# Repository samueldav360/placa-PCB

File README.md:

# placa-PCB
hize este proyecto para STASIS hackathon de hackclub

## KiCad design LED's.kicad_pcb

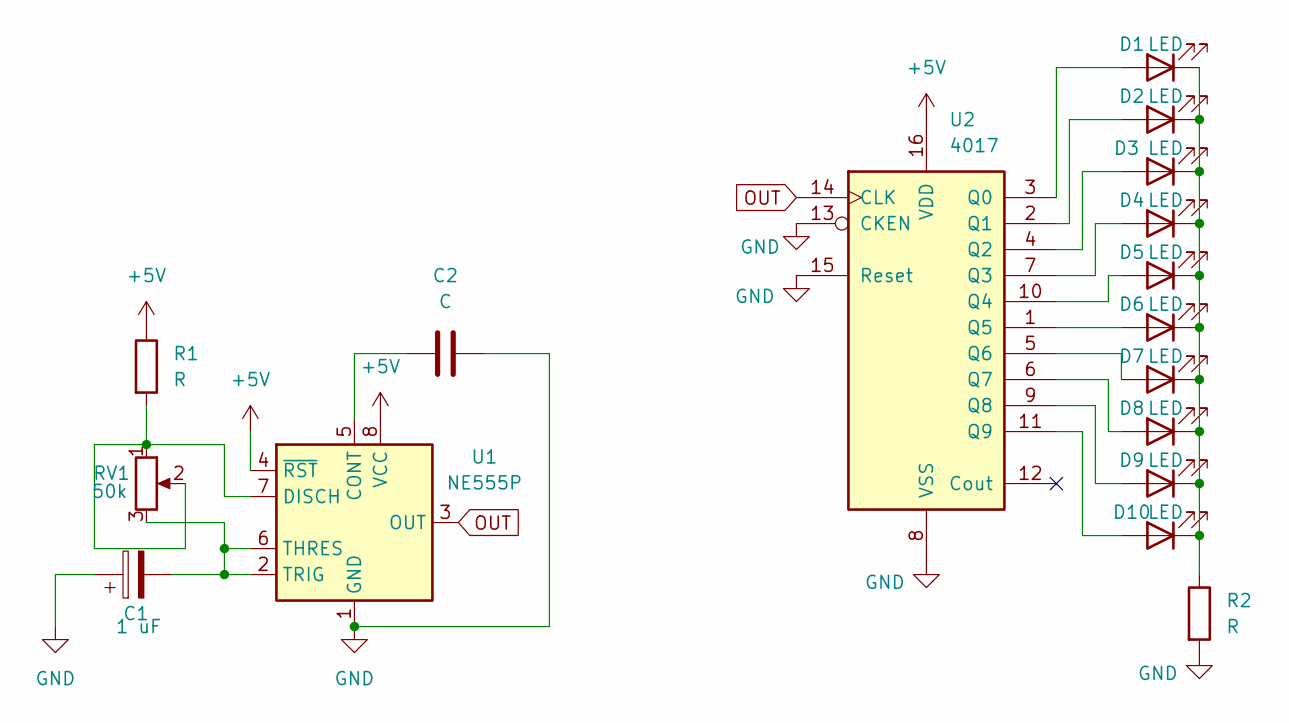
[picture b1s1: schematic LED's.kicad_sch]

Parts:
C1: 1 uF; C_Disc_D3.0mm_W1.6mm_P2.50mm
C2: C; C_Disc_D3.0mm_W1.6mm_P2.50mm
D1, D2, D3, D4, D5, D6, D7, D8, D9, D10: LED; LED_D3.0mm
R1, R2: R; R_Axial_DIN0204_L3.6mm_D1.6mm_P5.08mm_Horizontal
RV1: 50k; Potentiometer_ACP_CA6-VSMD_Vertical
U1: NE555P; DIP-8_W7.62mm
U2: 4017; N16

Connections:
+5V: R1.1, U1.4 (~RST), U1.8 (VCC), U2.16 (VDD)
GND: C1.1, C2.2, R2.2, U1.1 (GND), U2.8 (VSS), U2.13 (CKEN), U2.15 (Reset)
unnamed: D1.2 (A), U2.3 (Q0)
unnamed: D1.1 (K), D2.1 (K), D3.1 (K), D4.1 (K), D5.1 (K), D6.1 (K), D7.1 (K), D8.1 (K), D9.1 (K), D10.1 (K), R2.1
unnamed: D2.2 (A), U2.2 (Q1)
unnamed: D3.2 (A), U2.4 (Q2)
unnamed: D4.2 (A), U2.7 (Q3)
unnamed: D5.2 (A), U2.10 (Q4)
unnamed: D6.2 (A), U2.1 (Q5)
unnamed: D7.2 (A), U2.5 (Q6)
unnamed: D8.2 (A), U2.6 (Q7)
unnamed: D9.2 (A), U2.9 (Q8)
unnamed: D10.2 (A), U2.11 (Q9)
unnamed: C2.1, U1.5 (CONT)
unnamed: R1.2, RV1.1, RV1.2, U1.7 (DISCH)
unnamed: C1.2, RV1.3, U1.2 (TRIG), U1.6 (THRES)
OUT: U1.3 (OUT), U2.14 (CLK)

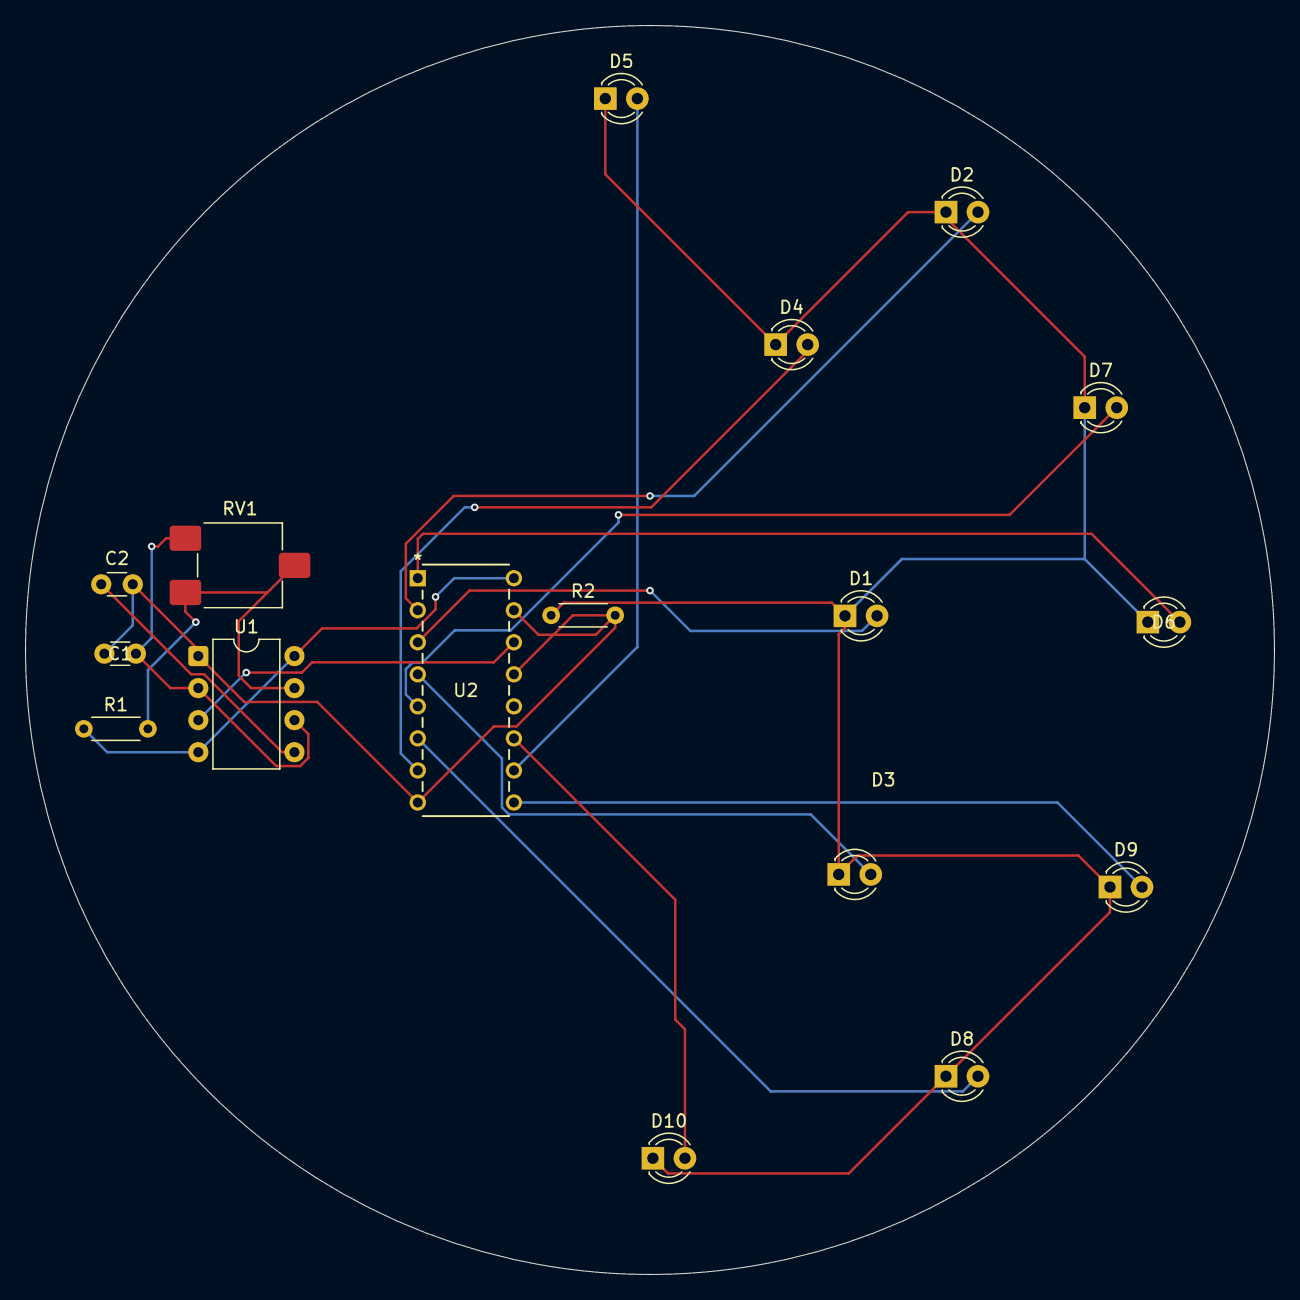
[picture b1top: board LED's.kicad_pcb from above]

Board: 2 copper layers, 99.0 x 99.0 mm, 17 parts (0 on the bottom side), 17 nets.
